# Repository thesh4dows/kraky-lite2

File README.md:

# kraky-lite2

Kraky-lite2 is the second version of the project kraky-lite.
The project Kraky-lite was inspired by Kraky, another project that i'm developing, and the focus
is to create a cheaper and DIY alternative for the flipper zero.

In this version the PCB is divided in 2 layers, one for power delivery and one for signal.

You can use it connected to a battery via the 18650 slot in the back or connected via usb-c.

I would soggest putting first all the smd commponents on the top layer, then the smd components on the bottom layer, and last the tht components.

I started this journey because i want to create a better version of my project kraky-lite, and i'm doing it by first using smd components instead of the 
tht modules so i can do some expirience soldering very small parts and stopping using pre made modules but recreating them myself.

---

# Main Components
| Function | Component |
|--------|----------|
| Logic board | **ESP32-S3 N16R8** |
| wifi | **nrf24l01** |
| Sub-GHz | **CC1101** |
| Battery charger | **CN3163** |
| Battery | **INR18650** |
| microSD Slot | **MSD4A** |
| Buttons | 1 tactile buttons and a rotary encoder |
| Display | TFT Display |
| COM converter | **CH343P** |

---

# WIRING DIAGRAM

# ESP32

 # POWER DELIVERY SYSTEM

# WIFI

# SUB-GHZ

# MICROSD SLOT

# DISPLAY

---

# PCB

---

# 3D render

---

# Responsible Use
Kraky-lite2 is built to make it easier for anyone to explore and understand how multifunction electronic devices work in everyday life. It’s not intended for bypassing security systems or breaking any laws.

All features are implemented with an educational and experimental focus.

---

# Tools Used

- KiCad 10
- Fusion360
- PlatformIO
---
## Contributing

All the Kraky's tools are an **open and educational project**.  
Feedback, suggestions, and improvements are always welcome.

---

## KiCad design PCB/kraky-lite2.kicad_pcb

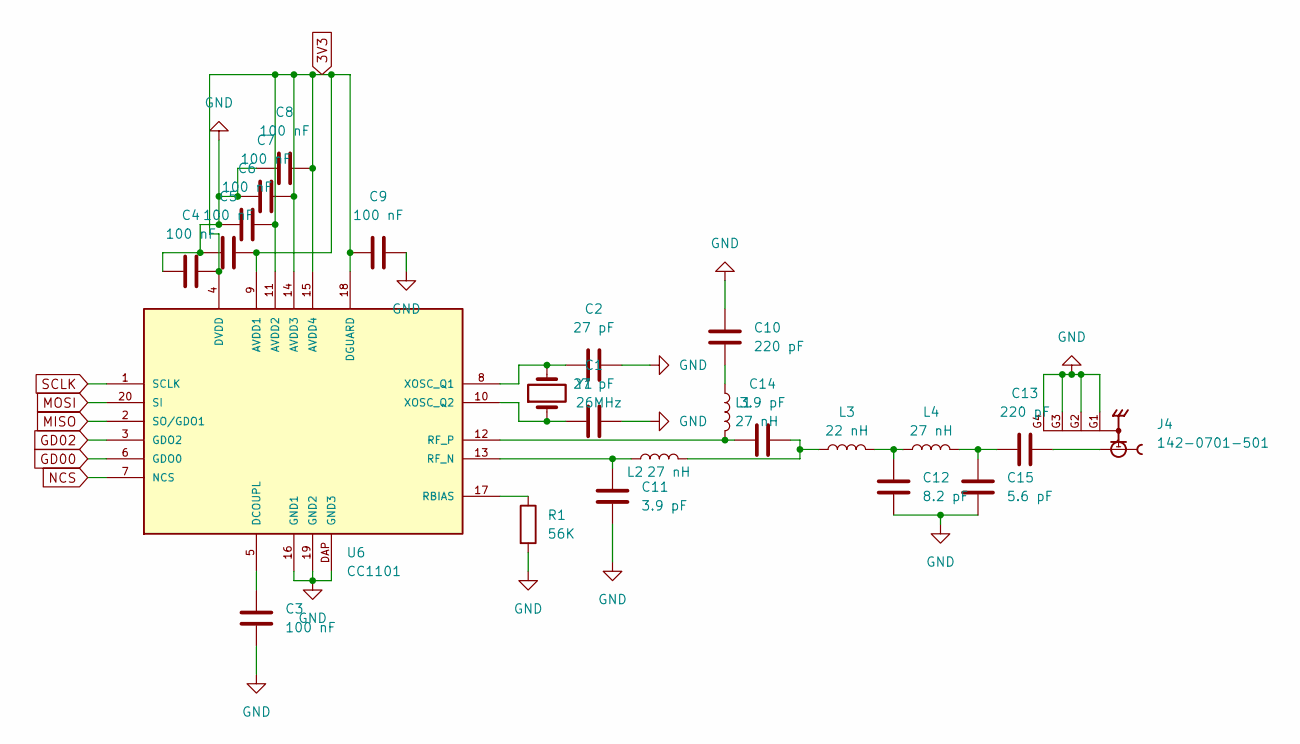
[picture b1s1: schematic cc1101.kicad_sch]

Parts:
C1, C2: 27 pF; C_0805_2012Metric
C3, C4, C5, C6, C7, C8, C9: 100 nF; C_0805_2012Metric
C10, C13: 220 pF; C_0805_2012Metric
C11, C14: 3.9 pF; C_0805_2012Metric
C12: 8.2 pF; C_0805_2012Metric
C15: 5.6 pF; C_0805_2012Metric
J4: 142-0701-501; SMA_Molex_73251-1153_EdgeMount_Horizontal; PARTREV 7c
L1, L2, L4: 27 nH; L_0805_2012Metric
L3: 22 nH; L_0805_2012Metric
R1: 56K; R_0805_2012Metric
U6: CC1101; QLP20
Y1: 26MHz; Crystal_SMD_5032-2Pin_5.0x3.2mm_HandSoldering

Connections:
3V3: C4.2, C5.2, C6.2, C7.2, C8.2, C9.2, U6.4 (DVDD), U6.9 (AVDD1), U6.11 (AVDD2), U6.14 (AVDD3), U6.15 (AVDD4), U6.18 (DGUARD); also elsewhere on the board
GD00: U6.6 (GDO0); also elsewhere on the board
GD02: U6.3 (GDO2); also elsewhere on the board
GND: C1.2, C2.2, C3.2, C4.1, C5.1, C6.1, C7.1, C8.1, C9.1, C10.2, C11.1, C12.2, C15.2, J4.G1, J4.G2, J4.G3, J4.G4, R1.2, U6.16 (GND1), U6.19 (GND2), U6.DAP (GND3); also elsewhere on the board
MISO: U6.2 (SO/GDO1); also elsewhere on the board
MOSI: U6.20 (SI); also elsewhere on the board
NCS: U6.7 (NCS); also elsewhere on the board
unnamed: C10.1, L1.1
unnamed: C12.1, L3.2, L4.1
unnamed: C13.1, C15.1, L4.2
unnamed: C13.2, J4.1
unnamed: C14.2, L2.2, L3.1
unnamed: C3.1, U6.5 (DCOUPL)
unnamed: R1.1, U6.17 (RBIAS)
unnamed: C11.2, L2.1, U6.13 (RF_N)
unnamed: C14.1, L1.2, U6.12 (RF_P)
unnamed: C2.1, U6.8 (XOSC_Q1), Y1.2
unnamed: C1.1, U6.10 (XOSC_Q2), Y1.1
SCLK: U6.1 (SCLK); also elsewhere on the board

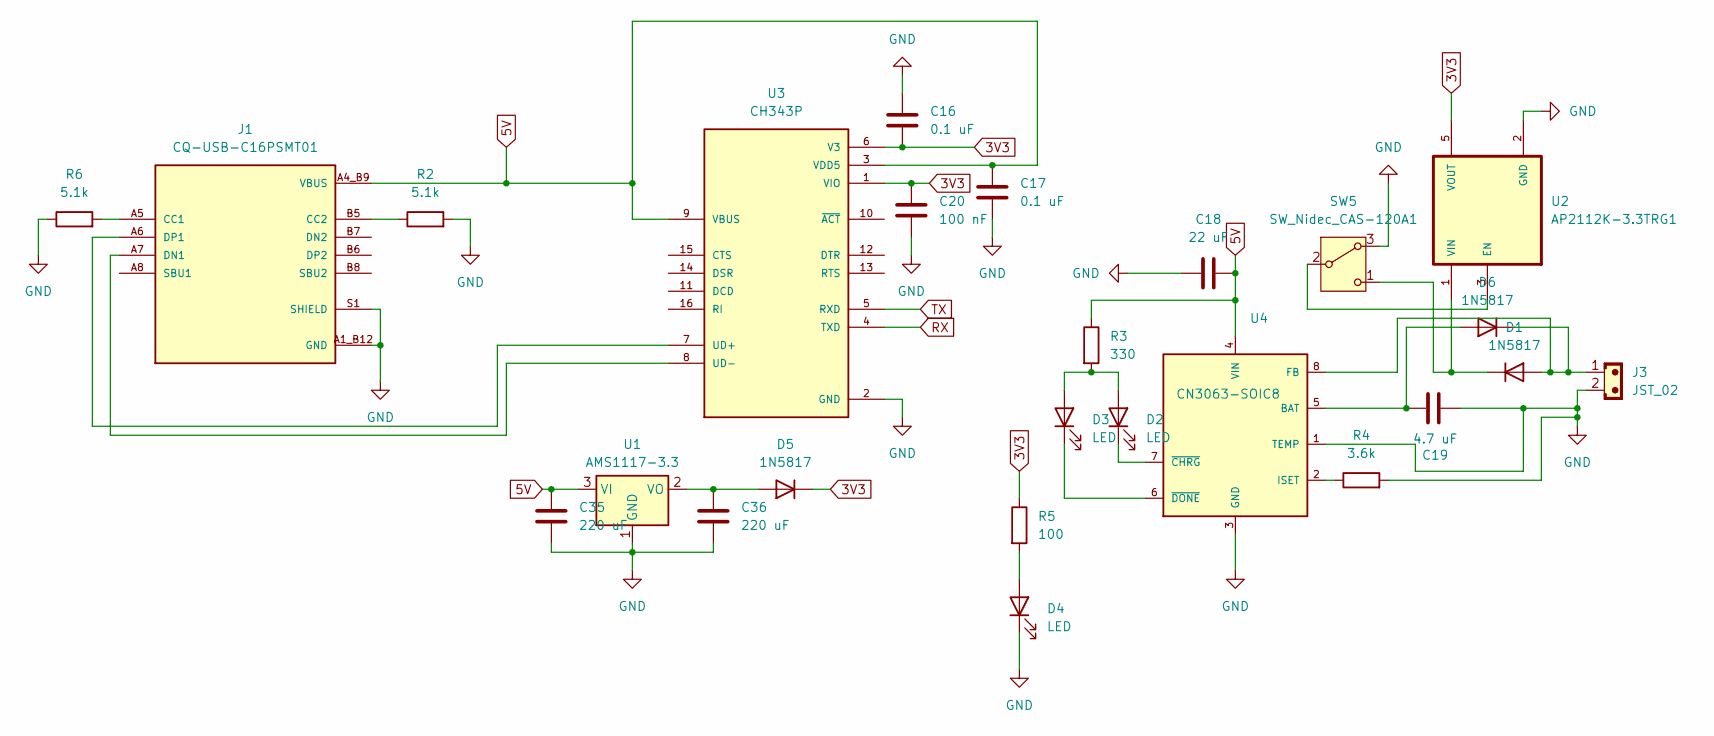
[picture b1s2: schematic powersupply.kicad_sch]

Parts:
C16, C17: 0.1 uF; C_0805_2012Metric
C18: 22 uF; C_0805_2012Metric
C19: 4.7 uF; C_0805_2012Metric
C20: 100 nF; C_0805_2012Metric
C35, C36: 220 uF; C_1210_3225Metric
D1, D5, D6: 1N5817; D_SMA_Handsoldering
D2, D3, D4: LED; LED_1206_3216Metric
J1: CQ-USB-C16PSMT01; SHENZHEN-CHUANGQIN-TECHNOLOGY_CQ-USB-C16PSMT01; PARTREV A
J3: JST_02; BatteryHolder_Keystone_1042_1x18650
R2, R6: 5.1k; R_0805_2012Metric
R3: 330; R_0805_2012Metric
R4: 3.6k; R_0805_2012Metric
R5: 100; R_0805_2012Metric
SW5: SW_Nidec_CAS-120A1; SW_Slide_SPDT_Angled_CK_OS102011MA1Q
U1: AMS1117-3.3; SOT-223-3_TabPin2
U2: AP2112K-3.3TRG1; SOT95P285X140-5N; PARTREV 2-2
U3: CH343P; QFN50P300X300X80-17N; PARTREV 1E
U4: CN3063-SOIC8; SOIC8-1.27-5X4MM; MPN CN3063

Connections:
3V3: C16.2, C20.1, D5.1 (K), R5.1, U2.5 (VOUT), U3.1 (VIO), U3.6 (V3); also elsewhere on the board
5V: C17.1, C18.2, C35.1, J1.A4_B9 (VBUS), J1.B4_A9 (VBUS), R3.1, U1.3 (VI), U3.3 (VDD5), U3.9 (VBUS), U4.4 (VIN)
GND: C16.1, C17.2, C18.1, C19.2, C20.2, C35.2, C36.2, D4.1 (K), J1.A1_B12 (GND), J1.B1_A12 (GND), J1.S1 (SHIELD), J1.S2 (SHIELD), J1.S3 (SHIELD), J1.S4 (SHIELD), J3.2, R2.2, R4.2, R6.1, SW5.3 (A), U1.1 (GND), U2.2 (GND), U3.2 (GND), U3.17 (GND), U4.1 (TEMP), U4.3 (GND); also elsewhere on the board
unnamed: D1.2 (A), D6.1 (K), J3.1, U4.8 (FB)
unnamed: D1.1 (K), SW5.1 (C), U2.1 (VIN)
unnamed: D2.2 (A), D3.2 (A), R3.2
unnamed: D2.1 (K), U4.7 (~CHRG)
unnamed: D3.1 (K), U4.6 (~DONE)
unnamed: D4.2 (A), R5.2
unnamed: C36.1, D5.2 (A), U1.2 (VO)
unnamed: C19.1, D6.2 (A), U4.5 (BAT)
unnamed: J1.A5 (CC1), R6.2
unnamed: J1.B5 (CC2), R2.1
unnamed: J1.A7 (DN1), U3.8 (UD-)
unnamed: J1.A6 (DP1), U3.7 (UD+)
unnamed: SW5.2 (B), U2.3 (EN)
unnamed: R4.1, U4.2 (ISET)
RX: U3.4 (TXD); also elsewhere on the board
TX: U3.5 (RXD); also elsewhere on the board

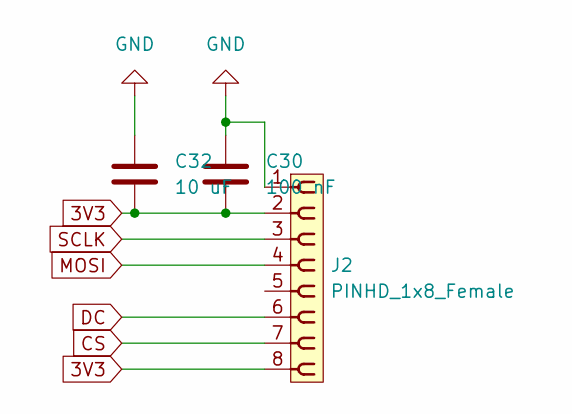
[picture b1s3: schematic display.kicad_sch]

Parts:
C30: 100 nF; C_0805_2012Metric
C32: 10 uF; C_0805_2012Metric
J2: PINHD_1x8_Female; PinSocket_1x08_P2.54mm_Vertical

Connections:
3V3: C30.2, C32.2, J2.2, J2.8; also elsewhere on the board
CS: J2.7; also elsewhere on the board
DC: J2.6; also elsewhere on the board
GND: C30.1, C32.1, J2.1; also elsewhere on the board
MOSI: J2.4; also elsewhere on the board
SCLK: J2.3; also elsewhere on the board

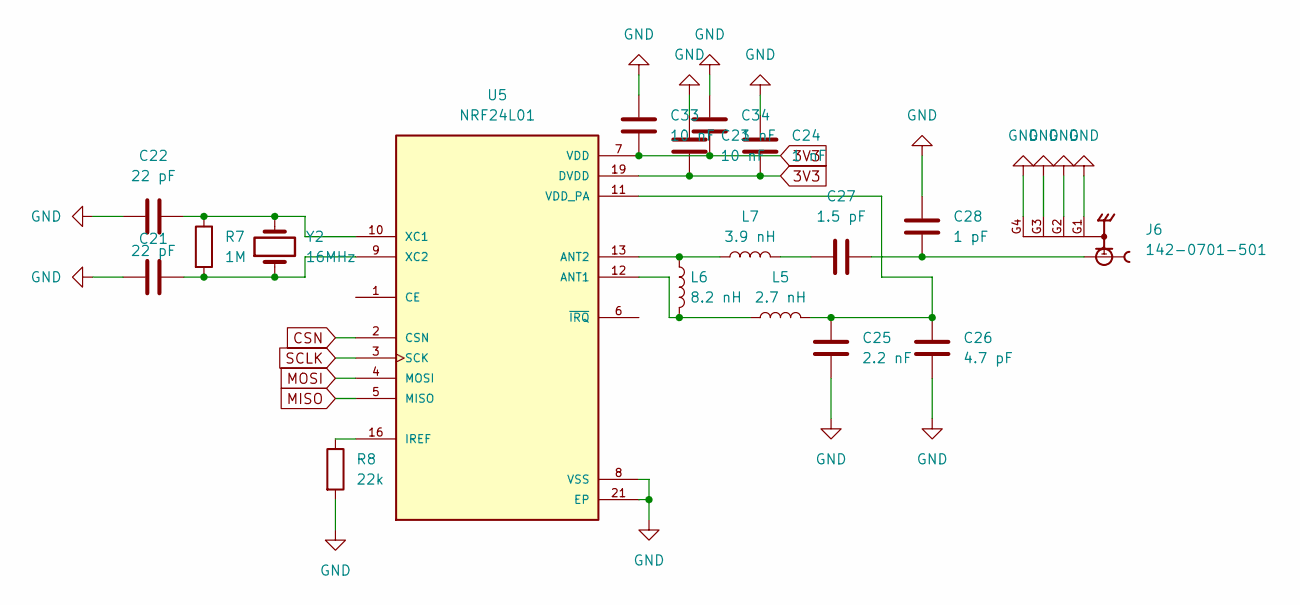
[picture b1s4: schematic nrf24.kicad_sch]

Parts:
C21, C22: 22 pF; C_0805_2012Metric
C23, C33: 10 nF; C_0805_2012Metric
C24, C34: 1 nF; C_0805_2012Metric
C25: 2.2 nF; C_0805_2012Metric
C26: 4.7 pF; C_0805_2012Metric
C27: 1.5 pF; C_0805_2012Metric
C28: 1 pF; C_0805_2012Metric
J6: 142-0701-501; SMA_Molex_73251-1153_EdgeMount_Horizontal; PARTREV 7c
L5: 2.7 nH; L_0805_2012Metric
L6: 8.2 nH; L_0805_2012Metric
L7: 3.9 nH; L_0805_2012Metric
R7: 1M; R_0805_2012Metric
R8: 22k; R_0805_2012Metric
U5: NRF24L01; QFN50P400X400X95-21N; PARTREV 2.0
Y2: 16MHz; Crystal_SMD_5032-2Pin_5.0x3.2mm_HandSoldering

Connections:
3V3: C23.2, C24.1, C33.2, C34.1, U5.7 (VDD), U5.15 (VDD), U5.18 (VDD), U5.19 (DVDD); also elsewhere on the board
CSN: U5.2 (CSN); also elsewhere on the board
GND: C21.1, C22.1, C23.1, C24.2, C25.2, C26.2, C28.1, C33.1, C34.2, J6.G1, J6.G2, J6.G3, J6.G4, R8.2, U5.8 (VSS), U5.14 (VSS), U5.17 (VSS), U5.20 (VSS), U5.21 (EP); also elsewhere on the board
MISO: U5.5 (MISO); also elsewhere on the board
MOSI: U5.4 (MOSI); also elsewhere on the board
unnamed: C27.1, L7.2
unnamed: C27.2, C28.2, J6.1
unnamed: L5.1, L6.2, U5.12 (ANT1)
unnamed: L6.1, L7.1, U5.13 (ANT2)
unnamed: R8.1, U5.16 (IREF)
unnamed: C25.1, C26.1, L5.2, U5.11 (VDD_PA)
unnamed: C22.2, R7.1, U5.10 (XC1), Y2.2
unnamed: C21.2, R7.2, U5.9 (XC2), Y2.1
SCLK: U5.3 (SCK); also elsewhere on the board

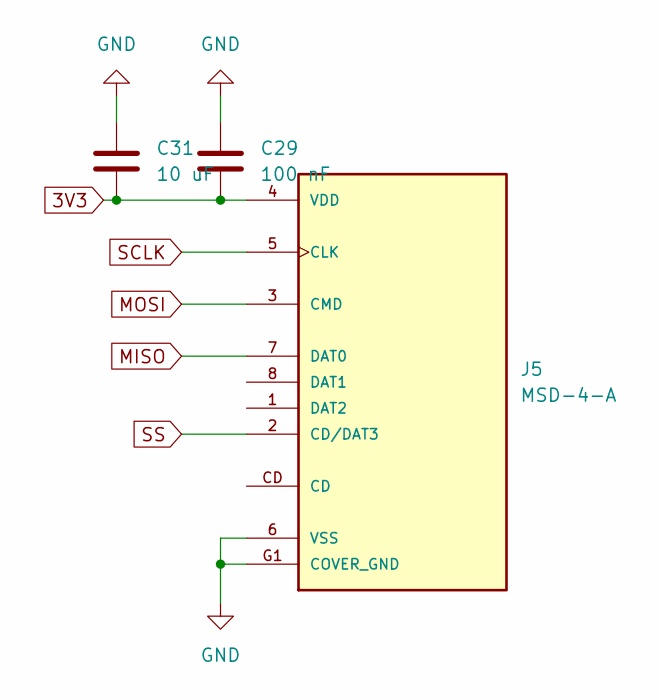
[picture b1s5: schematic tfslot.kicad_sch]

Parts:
C29: 100 nF; C_0805_2012Metric
C31: 10 uF; C_0805_2012Metric
J5: MSD-4-A; CUI_MSD-4-A; PARTREV 1.0

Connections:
3V3: C29.2, C31.2, J5.4 (VDD); also elsewhere on the board
GND: C29.1, C31.1, J5.6 (VSS), J5.G1 (COVER_GND), J5.G2 (COVER_GND), J5.G3 (COVER_GND), J5.G4 (COVER_GND); also elsewhere on the board
MISO: J5.7 (DAT0); also elsewhere on the board
MOSI: J5.3 (CMD); also elsewhere on the board
SCLK: J5.5 (CLK); also elsewhere on the board
SS: J5.2 (CD/DAT3); also elsewhere on the board

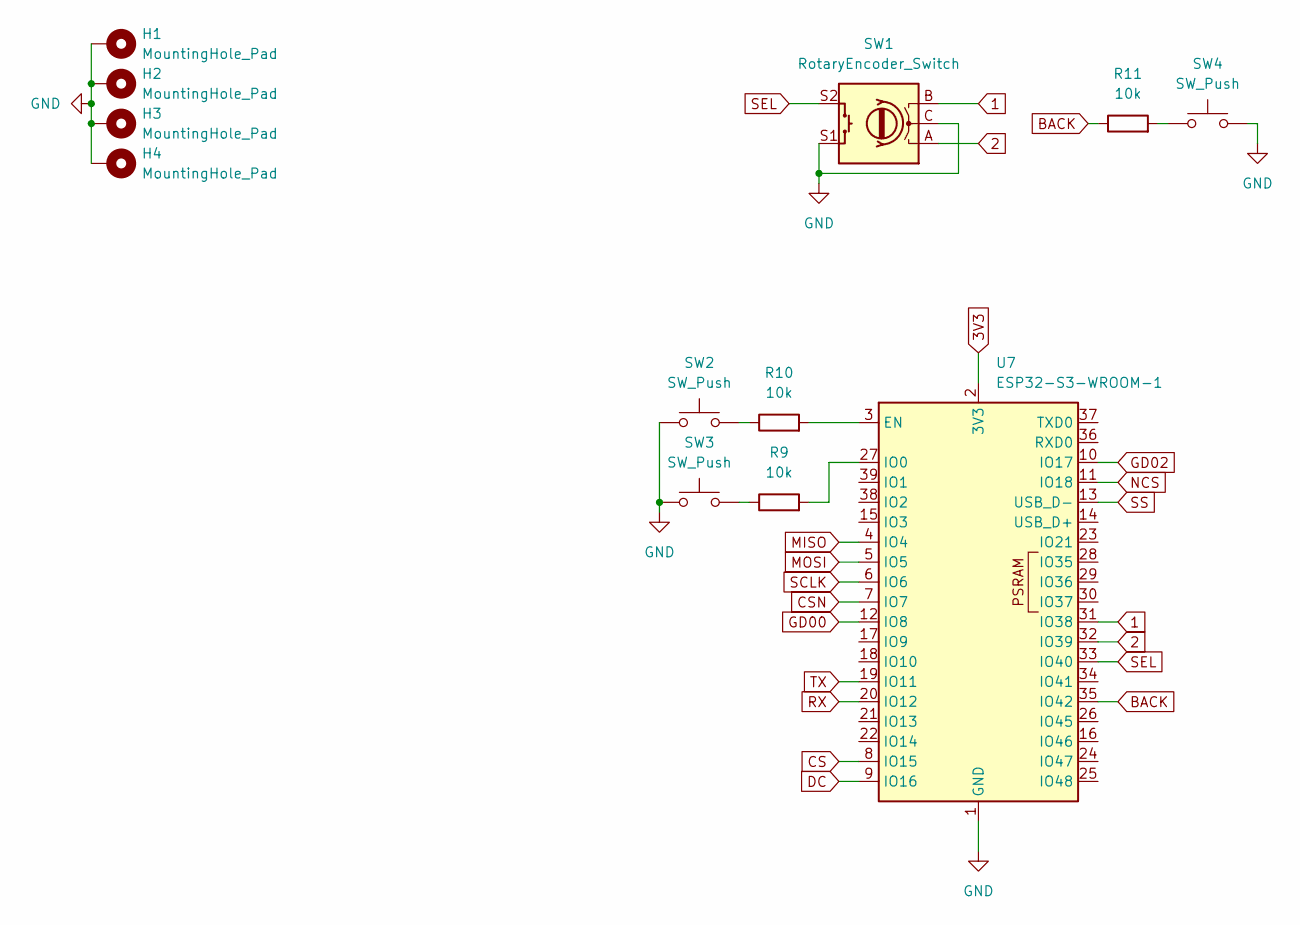
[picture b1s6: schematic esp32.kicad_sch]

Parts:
H1, H2, H3, H4: MountingHole_Pad; MountingHole_2.2mm_M2_DIN965_Pad
R9, R10, R11: 10k; R_0805_2012Metric
SW1: RotaryEncoder_Switch; RotaryEncoder_Alps_EC11E-Switch_Vertical_H20mm
SW2, SW3: SW_Push; SW_SPST_EVQPE1
SW4: SW_Push; SW_SPST_PTS645Sx43SMTR92
U7: ESP32-S3-WROOM-1

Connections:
1: SW1.B, U7.31 (IO38)
2: SW1.A, U7.32 (IO39)
3V3: U7.2 (3V3); also elsewhere on the board
BACK: R11.1, U7.35 (IO42)
CS: U7.8 (IO15); also elsewhere on the board
CSN: U7.7 (IO7); also elsewhere on the board
DC: U7.9 (IO16); also elsewhere on the board
GD00: U7.12 (IO8); also elsewhere on the board
GD02: U7.10 (IO17); also elsewhere on the board
GND: H1.1 (1_1), H2.1 (1_1), H3.1 (1_1), H4.1 (1_1), SW1.C, SW1.S1, SW2.1, SW3.1, SW4.2, U7.1 (GND), U7.40 (GND), U7.41 (GND); also elsewhere on the board
MISO: U7.4 (IO4); also elsewhere on the board
MOSI: U7.5 (IO5); also elsewhere on the board
NCS: U7.11 (IO18); also elsewhere on the board
unnamed: R9.1, SW3.2
unnamed: R10.1, SW2.2
unnamed: R11.2, SW4.1
unnamed: R10.2, U7.3 (EN)
unnamed: R9.2, U7.27 (IO0)
RX: U7.20 (IO12); also elsewhere on the board
SCLK: U7.6 (IO6); also elsewhere on the board
SEL: SW1.S2, U7.33 (IO40)
SS: U7.13 (USB_D-); also elsewhere on the board
TX: U7.19 (IO11); also elsewhere on the board

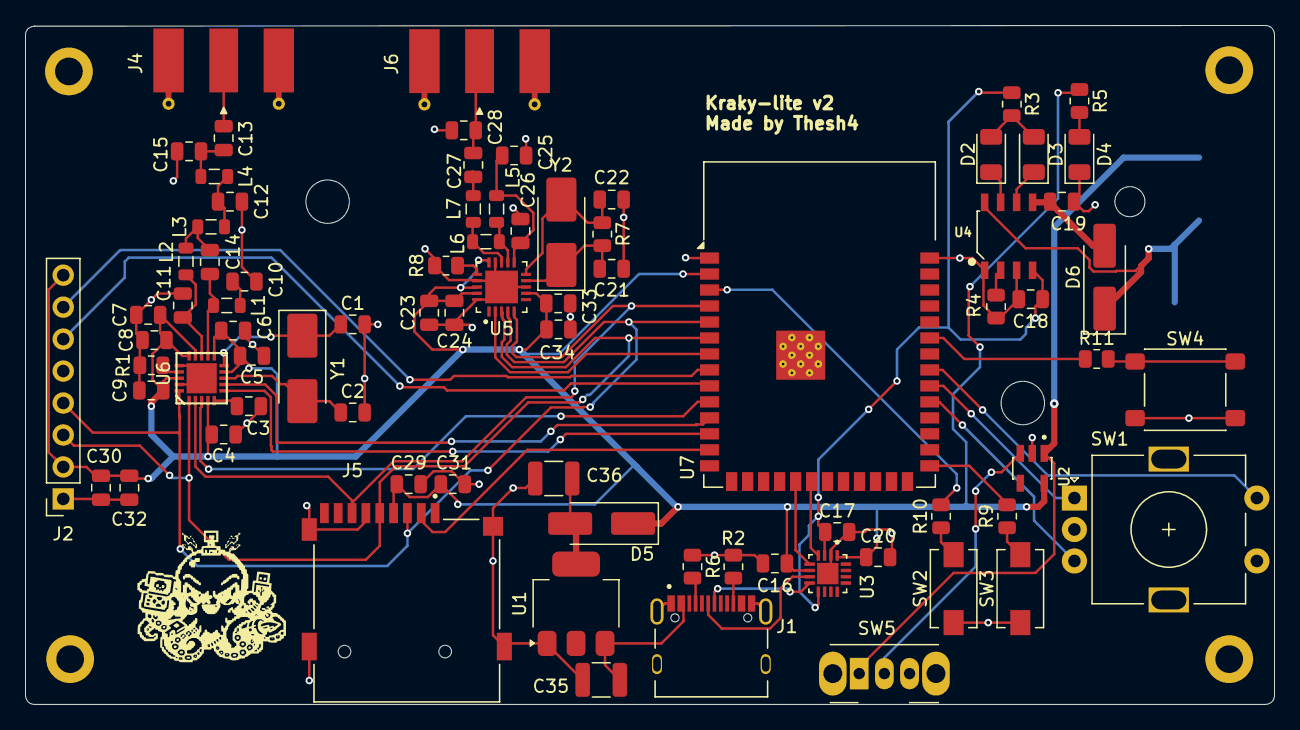
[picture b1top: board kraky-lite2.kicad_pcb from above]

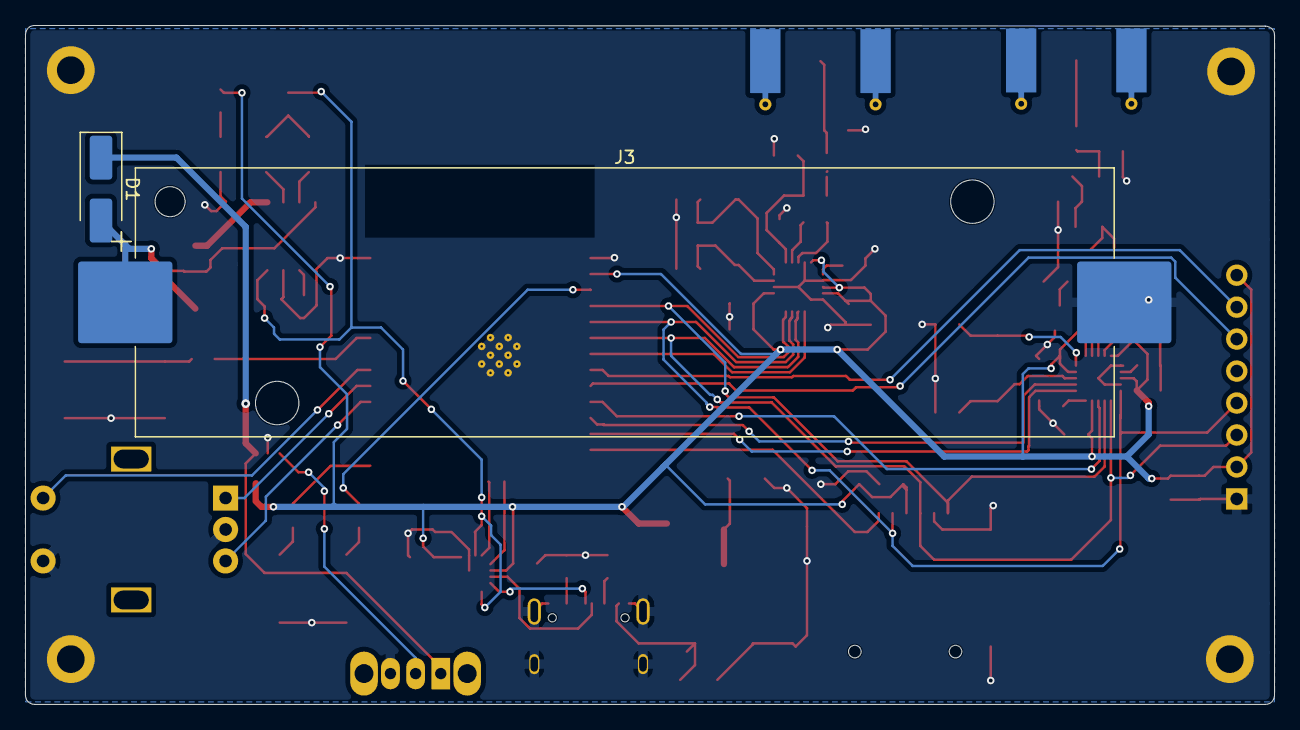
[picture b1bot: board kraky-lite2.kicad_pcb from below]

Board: 2 copper layers, 99.2 x 53.9 mm, 84 parts (2 on the bottom side), 57 nets.
